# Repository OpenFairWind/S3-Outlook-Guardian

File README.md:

# Signal K Outlook Guardian

The Outlook Guardian is a talking alarm annunciator for boats: an ESP32-S3 device that listens for vessel alarms and reads them out loud.

* Speaks the message of every [Signal K](https://signalk.org) notification that is raised
* Falls back to the NMEA 2000 alert messages (PGN 126983 and 126985) when the Signal K server is not connected
* Shows the severity of the alarm on the on-board RGB LED, which flashes red if the audio output fails to start
* Shows the IP address, the WiFi mode, the stream status and the latest notification on an optional SSD1306 OLED display
* Two push buttons acknowledge and snooze the alarms, and tell the Signal K server so
* The Signal K notification paths and the NMEA 2000 alert types to announce, and the welcome message, are chosen in the web interface
* Six languages (US and UK English, Italian, German, Spanish, French) with a choice of voice, speed and volume in the web interface
* Speech is synthesized on the device with PicoTTS and played through a MAX98357A I2S amplifier; no internet connection is needed

It is built with SensESP, and this repository is a fork of [SignalK/SensESP](https://github.com/SignalK/SensESP) that adds the application and the drivers it needs.

## Hardware

* ESP32-S3-DevKitC-1 N16R8 (16 MB flash, 8 MB PSRAM)
* MAX98357A I2S amplifier and a speaker
* 3.3 V CAN transceiver for the NMEA 2000 bus
* Two push buttons
* SSD1306 128x64 I2C OLED display (optional)

| Function | GPIO |
|----------|------|
| Amplifier LRC / BCLK / DIN | 4 / 5 / 6 |
| CAN TX / RX | 17 / 18 |
| Acknowledge button | 15 |
| Snooze button | 16 |
| Display SDA / SCL | 8 / 9 |
| RGB LED | 48 |

## Building and flashing

```sh
git clone --recursive https://github.com/OpenFairWind/S3-Outlook-Guardian.git
cd S3-Outlook-Guardian
pio run -e pioarduino_esp32s3 -t upload
```

The firmware is updated over USB. Over-the-air updates are not available, because the firmware with all six languages is too large to fit twice in the flash.

## Using it

On the first start the device opens a WiFi access point called `outlook-guardian`, with the password `thisisfine`, for entering the boat's WiFi settings at `http://192.168.4.1/`.
Approve its access request on the Signal K server with read/write permission, then open `http://outlook-guardian.local/` and choose the language and voice under *Speech and alarms*.

| LED | Meaning |
|-----|---------|
| Off | No alarm |
| Blue | Alert or caution |
| Yellow | Warning |
| Red | Alarm |
| Red, blinking fast | Emergency |

The LED blinks until the alarms have been acknowledged or snoozed.

## Outlook Guardian documentation

A step-by-step guide, from a bare board to a speaking device, is in [`docs/pages/outlook_guardian`](docs/pages/outlook_guardian/index.md):

1. [Assemble the hardware](docs/pages/outlook_guardian/hardware.md)
2. [Install the software and flash the firmware](docs/pages/outlook_guardian/building.md)
3. [Connect to WiFi and Signal K](docs/pages/outlook_guardian/first_start.md)
4. [Configure and test](docs/pages/outlook_guardian/usage.md)

Reference:

* [Alarm sources](docs/pages/outlook_guardian/alarm_sources.md) - how Signal K notifications and NMEA 2000 alerts are handled
* [Development notes](docs/pages/outlook_guardian/development.md) - code structure, languages and flash layout

## Status

The firmware builds, flashes and starts on the board. The audio output, the handling of live Signal K notifications and the reception of NMEA 2000 alerts have not yet been tested against real equipment.

## License

* Firmware and everything else in this repository: Apache License 2.0, see [LICENSE](LICENSE)
* Outlook Guardian board design in [hardware/outlook_guardian](hardware/outlook_guardian): [CC BY 4.0](https://creativecommons.org/licenses/by/4.0/), see [hardware/outlook_guardian/LICENSE](hardware/outlook_guardian/LICENSE)

# About SensESP

The rest of this file is the README of SensESP, the framework this project is built on.

## Introduction

**TL;DR: [Click here for the Getting Started documentation!](https://signalk.org/SensESP/pages/getting_started/)**

SensESP is a [Signal K](https://signalk.org) sensor development toolkit for the [ESP32](https://en.wikipedia.org/wiki/ESP32) platform.
If you are a boater (or a professional developer!) who wants to build a custom Wi-Fi connected sensor for your boat, this is the toolkit you need.
SensESP runs on commonly available ESP32 boards and helps you get sensor readings from physical sensors and transform them to meaningful data for Signal K or other outputs.

SensESP is built on the [Arduino](https://github.com/espressif/arduino-esp32) software development framework, a popular open source platform for embedded development.
(Note that this refers only to the software stack - Arduino hardware is not supported.)
To automate the management of external libraries, it also heavily relies on PlatformIO, a cross-platform build system for embedded devices (in other words, Arduino IDE is not supported).

SensESP features include:

* High-level programming interfaces for sensor development
* Support for a wide range of common sensor hardware with a set of [add-on libraries](https://signalk.org/SensESP/pages/additional_resources/) - and if native support is missing, using existing Arduino libraries directly is also quite simple in most cases
* A Web configuration user interface for sensors, transforms, and output paths
* Easy on-boarding with a Wi-Fi configuration tool and fully automated server discovery
* Full Signal K integration with authentication, and transmission and reception of data
* Support for over-the-air (OTA) firmware updates
* Support for remote debugging over Wi-Fi

To use SensESP, you need an ESP32 development board and a way to power it from the boat's 12V or 24V nominal power system.
This can be done with commonly available ESP32DevKit boards and external DC-DC converters, or alternatively, the [Sailor Hat with ESP32 (SH-ESP32)](https://hatlabs.fi/product/sailor-hat-with-esp32/) has all these features baked into a developer-friendly board and enclosure kit.

Example use cases of SensESP include:

* Engine temperature measurement
* Switch input for bilge alarms
* Device control using relays
* Custom GPS and attitude sensors
* Engine RPM measurement
* Anchor chain counter
* Battery voltage and current measurement
* Tank level measurement
* Custom NMEA 2000 sensors

At heart, SensESP is a development toolkit, and not ready-made software.
This means that you will need to do some simple programming to use it.
Don't worry, though.
The project is newbie-friendly, so you don't need to know much to get started.
A lot of examples and tutorials are provided, and some related projects also provide ready-to-use firmware for specific use cases.

> **Prefer an AI-assisted path?** The [SensESP Workspace](https://github.com/hatlabs/SensESP-workspace)
> is a [Claude Code](https://code.claude.com/docs/en/quickstart) environment that
> guides you from a natural-language description of what you want to build all the
> way to firmware flashed on your device — no prior embedded experience required.
> It supports Hat Labs boards (HALMET, HALSER, SH-ESP32, SH-wg) and generic ESP32s.

## Documentation

To get started, [see the project documentation](https://signalk.org/SensESP/).

For reference, the old SensESP version 1 documentation is still available at the [repository wiki](https://github.com/SignalK/SensESP/wiki).

## Getting help

Discussion about SensESP happens mostly on the [Signal K Discord](https://discord.com/channels/1170433917761892493/1170433918592368684) on the #sensesp channel. To register as a new user, follow the invite link at [signalk.org](https://signalk.org/).

Another place for SensESP discussions is the [discussion board on the SensESP GitHub repository](https://github.com/SignalK/SensESP/discussions).

## Version 3

SensESP v3 is the current major version. Key changes from v2 include:

- Web frontend rewritten with Preact and Bootstrap, replacing the old JSONEditor-based UI
- Built-in WiFi manager replacing the external WiFiManager library, with simultaneous AP+STA support
- Explicit `ConfigItem` system for exposing objects to the web configuration UI
- Transport-agnostic networking supporting both WiFi and Ethernet
- New transforms: Join, Zip, Filter, Throttle, Repeat variants, Hysteresis
- Standard ESP-IDF logging replacing RemoteDebug

For migration instructions from v2, see the [Migration Guide](https://signalk.org/SensESP/pages/migration/).

### Development

The frontend project is in the `frontend` directory tree. To build the frontend,
you need to have Node and `pnpm` installed. Install the required dependencies:

```sh
./run install-frontend
```

Then build the frontend:

```sh
./run build-frontend
```

This will both build the project and save the deployment files in C++ source files suitable for embedding in the SensESP firmware.

To start the development server, run:

```sh
cd frontend
pnpm run dev
```

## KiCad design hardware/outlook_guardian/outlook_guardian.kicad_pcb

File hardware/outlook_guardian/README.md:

# Outlook Guardian board

A KiCad 10 project for a single board that replaces the breadboard build described in
[the hardware guide](../../docs/pages/outlook_guardian/hardware.md).

**Status: revision 0.1, not yet built.** The schematic passes ERC and the board passes DRC, but no
board has been made and no engineer has reviewed the layout. Read [Before ordering](#before-ordering)
first.

## Form factor

The board follows the [Hat Labs HALMET](https://github.com/hatlabs/HALMET-hardware) (CC BY 4.0), so it
fits the same 100 x 68 x 50 mm enclosure. These are at HALMET's exact positions:

- the outline (89 x 58 mm, concave corners, tab on the right) and the two M3 slots,
- the module, with its antenna overhanging the board edge,
- the 2x10 GPIO header and the 1x4 display socket, with the same power and ground pins,
- the NMEA 2000 terminal block (GND, V+, CAN-H, CAN-L), the USB socket, the BOOT and RESET buttons
  and the EN/IO0 header.

HALMET uses an ESP32; this board uses the ESP32-S3-WROOM-1-N16R8 the firmware needs. The module
outline is the same, but the GPIO numbers are not, so the signal pins of the headers carry ESP32-S3
pins.

## Pins

The on-board functions use the pins the firmware already defaults to, so no build flag changes.

| Function | GPIO |
|----------|------|
| Amplifier LRC, BCLK, DIN | 4, 5, 6 |
| Display SDA, SCL | 8, 9 |
| Acknowledge, Snooze buttons | 15, 16 |
| CAN TX, RX | 17, 18 |
| USB D-, D+ | 19, 20 |
| RGB LED (SK6812) | 48 |
| BOOT button | 0 |

GPIO header (J3), pin 1 is the square pad:

| Pin | Signal | Pin | Signal |
|-----|--------|-----|--------|
| 1 | 3V3 | 2 | IO21 |
| 3 | GND | 4 | IO1 |
| 5 | IO11 | 6 | IO2 |
| 7 | IO12 | 8 | IO7 |
| 9 | IO13 | 10 | IO10 |
| 11 | IO14 | 12 | GND |
| 13 | IO41 (MTDI) | 14 | GND |
| 15 | IO40 (MTDO) | 16 | GND |
| 17 | IO39 (MTCK) | 18 | GND |
| 19 | IO42 (MTMS) | 20 | 3V3 |

Display socket (J5): GND, 3V3, SCL, SDA, with GND next to the BOOT button. UART0 TX and RX, 5 V,
3.3 V and GND are on test pads on the back.

## Circuit

- **Supply, 9 to 32 V:** resettable fuse, TVS diode, reverse-polarity Schottky, input filter, then an
  XL1509-5.0 buck converter to 5 V (the converter HALMET uses, in its 5 V version).
- **3.3 V:** linear regulator from 5 V.
- **USB:** Micro-B on the ESP32-S3's native USB, with ESD protection. USB also powers the board
  through a fuse and a diode, so USB and the boat supply can be connected together.
- **Audio:** MAX98357A at 5 V, ferrite beads and capacitors on the speaker outputs.
- **NMEA 2000:** SN65HVD230 with a TVS diode, no termination resistor.
- **Buttons:** pull-up, series resistor, capacitor and ESD diode on each input.

## Files

| File | Content |
|------|---------|
| `outlook_guardian.kicad_pro`, `.kicad_sch`, `.kicad_pcb` | The project: open the `.kicad_pro` in KiCad |
| `OutlookGuardian.pretty/` | The mounting slot and the module footprint with a narrower antenna keep-out |
| `fab/` | Gerbers and drill files (also zipped), BOM, placement file, schematic and assembly PDFs, renders |
| `tools/` | The scripts that generated the project |

The board has four layers: signals and ground pour on the outer layers, a ground plane on inner
layer 1, and 3.3 V with a 5 V area on inner layer 2.

## Regenerating

The schematic and the board were generated by the scripts in `tools/` and can be edited in KiCad like
any other project. **Running the scripts again overwrites edits made in KiCad.**

```bash
tools/check.sh    # schematic from tools/design.py, then ERC
tools/route.sh    # board from the schematic and tools/placement.py, autoroute, DRC
tools/fab.sh      # fabrication files into fab/
```

`route.sh` needs Java and the [Freerouting](https://github.com/freerouting/freerouting) 1.9.0 jar; set
`FREEROUTING` to its path. Later Freerouting versions did not terminate on this board.

## Before ordering

Checked by tools:

- ERC: one warning, the pin type of the amplifier's thermal pad in KiCad's own symbol.
- The netlist exported from the schematic matches `tools/design.py` on every pin.
- DRC: no violations, no unconnected items, no schematic mismatch, at 0.2 mm track and clearance,
  0.6/0.3 mm vias.

Not checked, and needing a person:

1. **Layout review.** The tracks come from an autorouter. Look at the buck converter loop (U1, D3,
   L2, C2 to C4), the speaker outputs and the USB pair, which is not routed as a differential pair.
2. **Antenna.** The USB socket is within the 15 mm clearance Espressif recommends around the antenna,
   as on HALMET. The module footprint's keep-out was narrowed to allow it.
3. **Part numbers.** They are in the `MPN` field. Ratings were checked against distributor listings
   for F1 and L2 only. None has a supplier order code, and none was checked for stock.
4. **F1 and D1 at 24 V.** F1 is rated 33 V and D1 is an SMBJ33CA, close to the 32 V top of the range.
   For a 24 V boat, choose a 60 V fuse and check the clamp voltage against U1's 40 V maximum.
5. **U2 output capacitor.** Confirm in the AZ1117C datasheet that it is stable with ceramic
   capacitors, or change C10.
6. **USB back-feed.** With USB only, 5 V reaches the output of U1 through L2. Confirm that the
   XL1509 tolerates this, or add a diode.
7. **Display clearance.** Check the height of the parts under the display module once its
   orientation on the socket is known.
8. **A first board is a prototype.** Bring it up on a bench supply with a current limit before
   connecting it to a boat.

## Licence

The Outlook Guardian board design in this directory (schematic, PCB layout, footprints and
fabrication outputs) is licensed under
[CC BY 4.0](https://creativecommons.org/licenses/by/4.0/); the full text is in [LICENSE](LICENSE).

The outline and the connector positions derive from the Hat Labs HALMET hardware design, also
licensed under CC BY 4.0.

This covers the hardware only. The firmware in the rest of the repository stays under the
Apache License 2.0, as in the [LICENSE](../../LICENSE) file at the repository root.

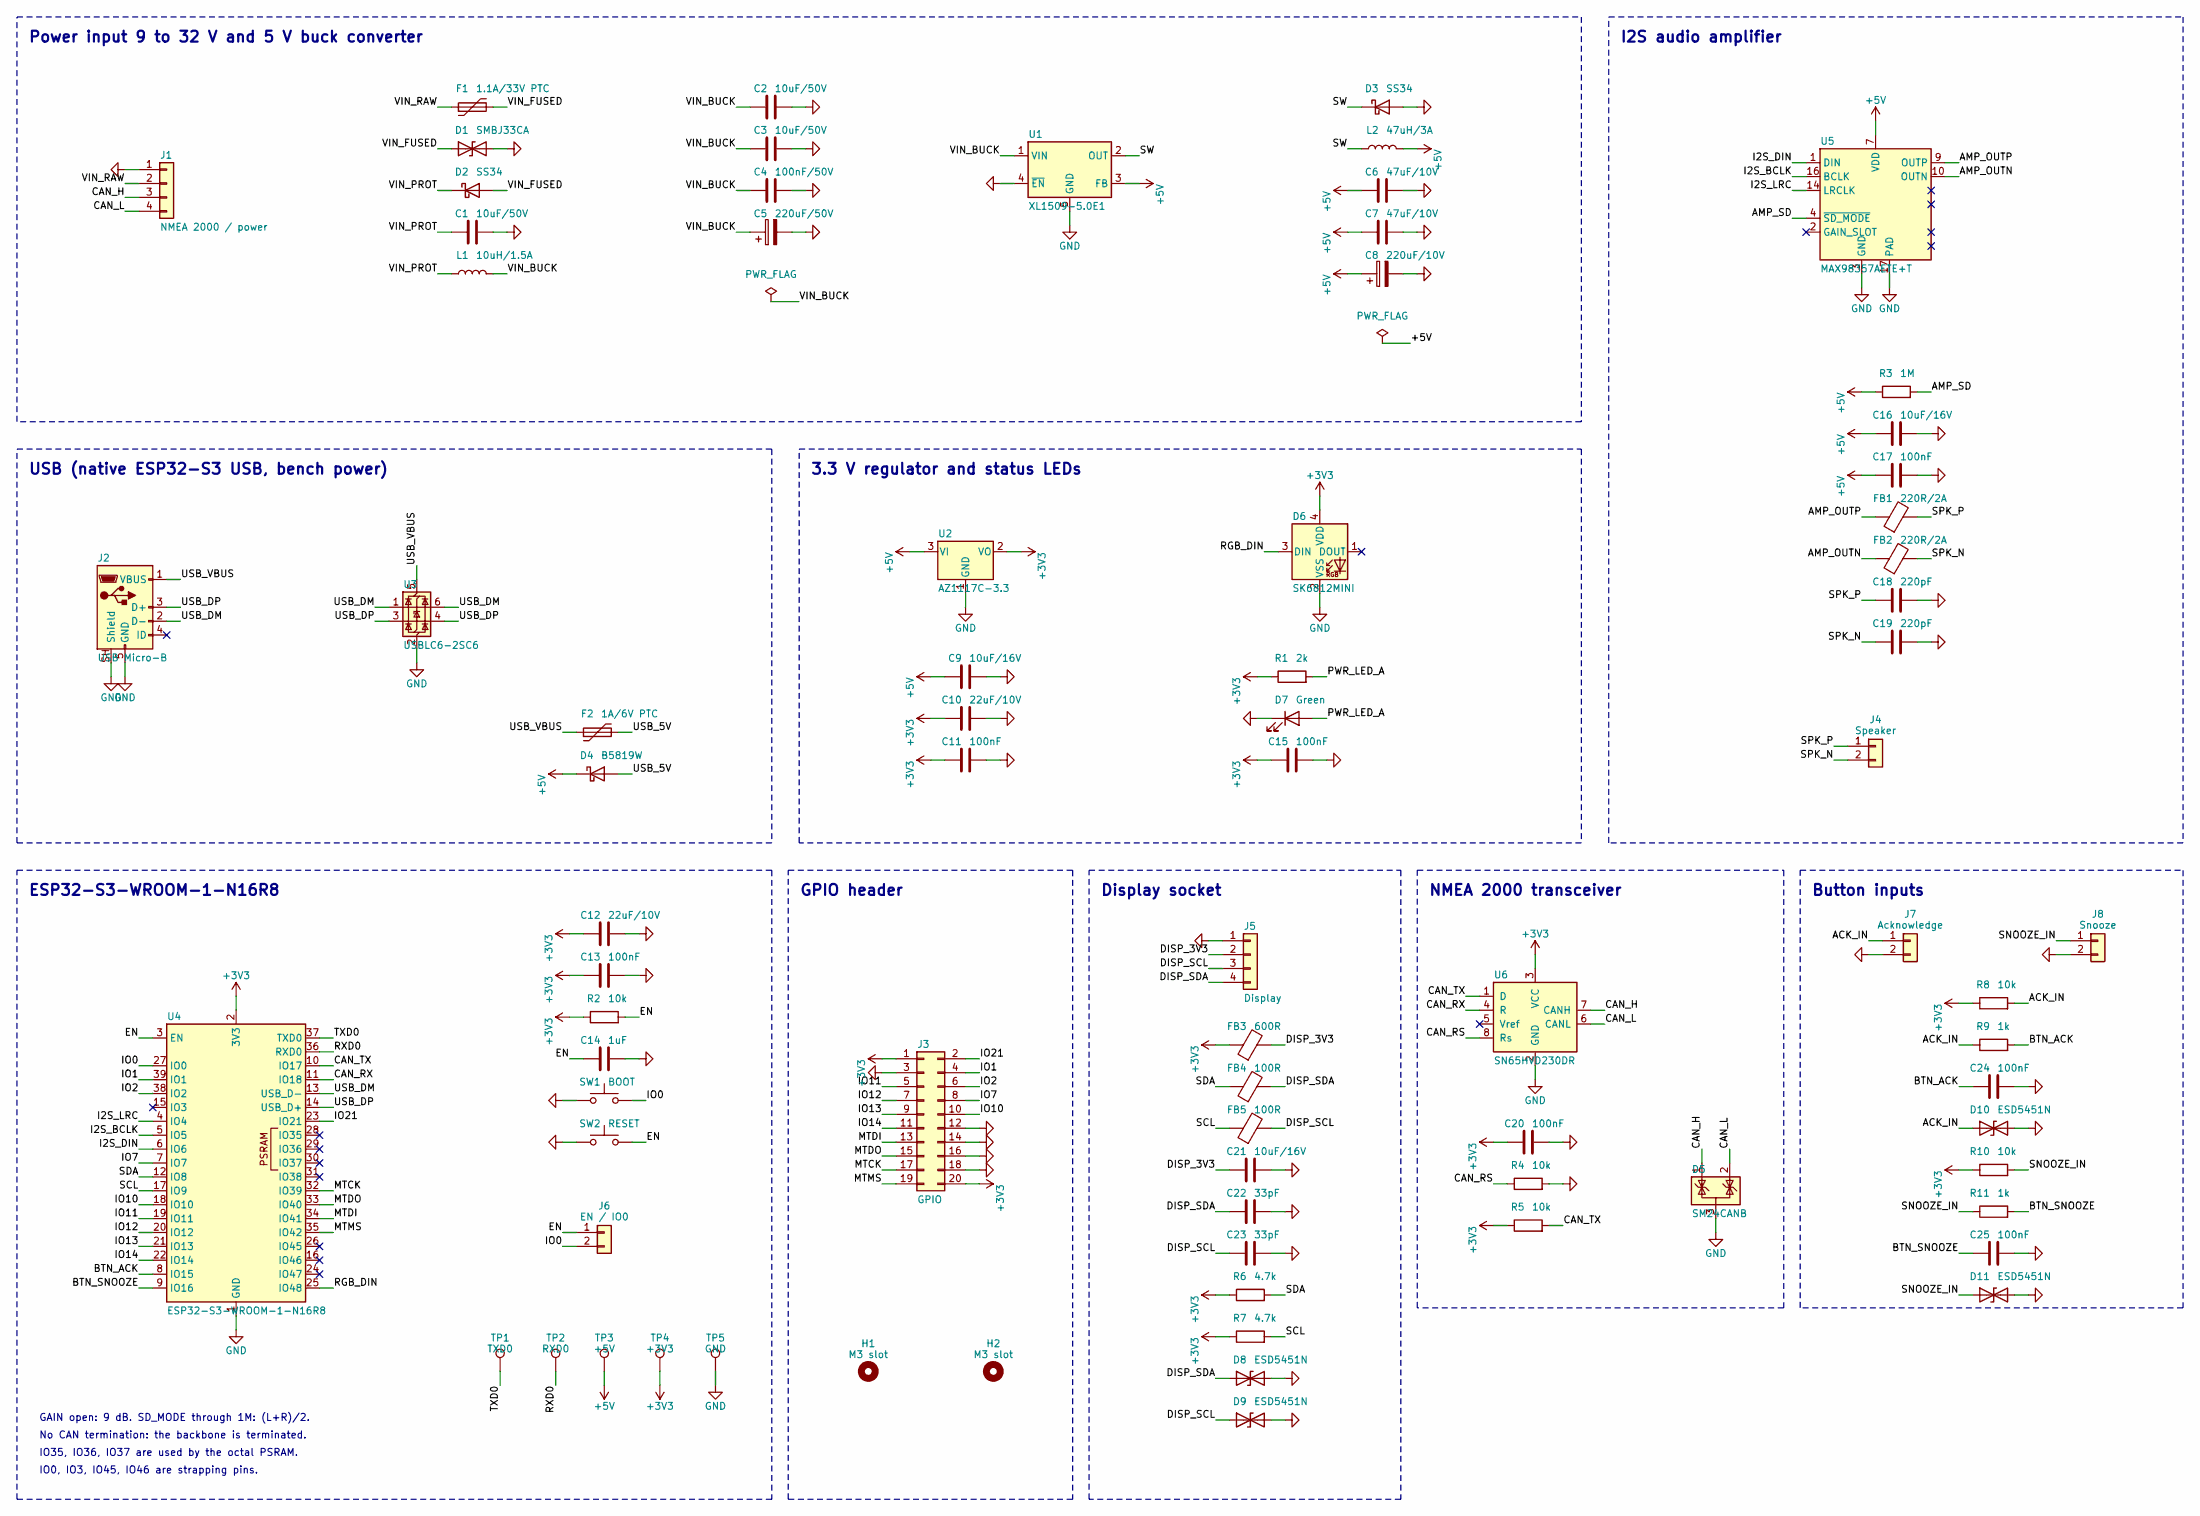
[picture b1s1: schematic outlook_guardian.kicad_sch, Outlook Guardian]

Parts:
C1, C2, C3: 10uF/50V; C_1206_3216Metric
C4: 100nF/50V; C_0603_1608Metric
C5: 220uF/50V; CP_Elec_10x10.5
C6, C7: 47uF/10V; C_1206_3216Metric
C8: 220uF/10V; CP_Elec_6.3x7.7
C9, C16, C21: 10uF/16V; C_0805_2012Metric
C10, C12: 22uF/10V; C_0805_2012Metric
C11, C13, C15, C17, C20, C24, C25: 100nF; C_0603_1608Metric
C14: 1uF; C_0603_1608Metric
C18, C19: 220pF; C_0603_1608Metric
C22, C23: 33pF; C_0603_1608Metric
D1: SMBJ33CA; D_SMB; MPN SMBJ33CA
D2, D3: SS34; D_SMA; MPN SS34
D4: B5819W; D_SOD-123; MPN B5819W
D5: SM24CANB; SOT-23; MPN SM24CANB-02HTG
D6: SK6812MINI; LED_SK6812MINI_PLCC4_3.5x3.5mm_P1.75mm; MPN SK6812MINI
D7: Green; LED_0603_1608Metric
D8, D9, D10, D11: ESD5451N; D_0402_1005Metric; MPN ESD5451N
F1: 1.1A/33V PTC; Fuse_1812_4532Metric; MPN 1812L110/33MR
F2: 1A/6V PTC; Fuse_1206_3216Metric; MPN BSMD1206-100-6V
FB1, FB2: 220R/2A; L_0805_2012Metric; MPN BLM21PG221SN1D
FB3: 600R; L_0805_2012Metric; MPN GZ2012D601TF
FB4, FB5: 100R; L_0805_2012Metric; MPN GZ2012D101TF
H1, H2: M3 slot; MountingSlot_3.2mm_M3_Unplated
J1: NMEA 2000 / power; PhoenixContact_MCV_1,5_4-G-3.81_1x04_P3.81mm_Vertical; MPN Phoenix MCV 1,5/4-G-3,81
J2: USB Micro-B; USB_Micro-B_Wuerth_614105150721_Vertical; MPN Wuerth 614105150721
J3: GPIO; PinHeader_2x10_P2.54mm_Vertical
J4: Speaker; PhoenixContact_MCV_1,5_2-G-3.81_1x02_P3.81mm_Vertical; MPN Phoenix MCV 1,5/2-G-3,81
J5: Display; PinSocket_1x04_P2.54mm_Vertical
J6: EN / IO0; PinHeader_1x02_P2.54mm_Vertical
J7: Acknowledge; PhoenixContact_MCV_1,5_2-G-3.81_1x02_P3.81mm_Vertical; MPN Phoenix MCV 1,5/2-G-3,81
J8: Snooze; PhoenixContact_MCV_1,5_2-G-3.81_1x02_P3.81mm_Vertical; MPN Phoenix MCV 1,5/2-G-3,81
L1: 10uH/1.5A; L_Bourns-SRN4018; MPN SRN4018-100M
L2: 47uH/3A; L_Bourns_SRR1260; MPN SRR1260-470M
R1: 2k; R_0603_1608Metric
R2, R4, R5, R8, R10: 10k; R_0603_1608Metric
R3: 1M; R_0603_1608Metric
R6, R7: 4.7k; R_0603_1608Metric
R9, R11: 1k; R_0603_1608Metric
SW1: BOOT; SW_SPST_TL3342; MPN TL3342F160QG
SW2: RESET; SW_SPST_TL3342; MPN TL3342F160QG
TP1: TXD0; TestPoint_Pad_D1.5mm
TP2: RXD0; TestPoint_Pad_D1.5mm
TP3: +5V; TestPoint_Pad_D1.5mm
TP4: +3V3; TestPoint_Pad_D1.5mm
TP5: GND; TestPoint_Pad_D1.5mm
U1: XL1509-5.0E1; SOIC-8_3.9x4.9mm_P1.27mm; MPN XL1509-5.0E1
U2: AZ1117C-3.3; SOT-223-3_TabPin2; MPN AZ1117CH-3.3TRG1
U3: USBLC6-2SC6; SOT-23-6; MPN USBLC6-2SC6
U4: ESP32-S3-WROOM-1-N16R8; ESP32-S3-WROOM-1_EdgeAntenna; MPN ESP32-S3-WROOM-1-N16R8
U5: MAX98357AETE+T; TQFN-16-1EP_3x3mm_P0.5mm_EP1.23x1.23mm; MPN MAX98357AETE+T
U6: SN65HVD230DR; SOIC-8_3.9x4.9mm_P1.27mm; MPN SN65HVD230DR

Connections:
+3V3: C10.1, C11.1, C12.1, C13.1, C15.1, C20.1, D6.4 (VDD), FB3.1, J3.1, J3.20, R1.1, R2.1, R5.1, R6.1, R7.1, R8.1, R10.1, TP4.1, U2.2 (VO), U4.2 (3V3), U6.3 (VCC)
+5V: C6.1, C7.1, C8.1, C9.1, C16.1, C17.1, D4.1 (K), L2.2, R3.1, TP3.1, U1.3 (FB), U2.3 (VI), U5.7 (VDD), U5.8 (VDD)
/ACK_IN: D10.1 (A1), J7.1, R8.2, R9.1
/AMP_OUTN: FB2.1, U5.10 (OUTN)
/AMP_OUTP: FB1.1, U5.9 (OUTP)
/AMP_SD: R3.2, U5.4 (~SD_MODE)
/BTN_ACK: C24.1, R9.2, U4.8 (IO15)
/BTN_SNOOZE: C25.1, R11.2, U4.9 (IO16)
/CAN_H: D5.1 (K), J1.3, U6.7 (CANH)
/CAN_L: D5.2 (K), J1.4, U6.6 (CANL)
/CAN_RS: R4.1, U6.8 (Rs)
/CAN_RX: U4.11 (IO18), U6.4 (R)
/CAN_TX: R5.2, U4.10 (IO17), U6.1 (D)
/DISP_3V3: C21.1, FB3.2, J5.2
/DISP_SCL: C23.1, D9.1 (A1), FB5.2, J5.3
/DISP_SDA: C22.1, D8.1 (A1), FB4.2, J5.4
/EN: C14.1, J6.1, R2.2, SW2.2, U4.3 (EN)
/I2S_BCLK: U4.5 (IO5), U5.16 (BCLK)
/I2S_DIN: U4.6 (IO6), U5.1 (DIN)
/I2S_LRC: U4.4 (IO4), U5.14 (LRCLK)
/IO0: J6.2, SW1.2, U4.27 (IO0)
/IO1: J3.4, U4.39 (IO1)
/IO2: J3.6, U4.38 (IO2)
/IO7: J3.8, U4.7 (IO7)
/IO10: J3.10, U4.18 (IO10)
/IO11: J3.5, U4.19 (IO11)
/IO12: J3.7, U4.20 (IO12)
/IO13: J3.9, U4.21 (IO13)
/IO14: J3.11, U4.22 (IO14)
/IO21: J3.2, U4.23 (IO21)
/MTCK: J3.17, U4.32 (IO39)
/MTDI: J3.13, U4.34 (IO41)
/MTDO: J3.15, U4.33 (IO40)
/MTMS: J3.19, U4.35 (IO42)
/PWR_LED_A: D7.2 (A), R1.2
/RGB_DIN: D6.3 (DIN), U4.25 (IO48)
/RXD0: TP2.1, U4.36 (RXD0)
/SCL: FB5.1, R7.2, U4.17 (IO9)
/SDA: FB4.1, R6.2, U4.12 (IO8)
/SNOOZE_IN: D11.1 (A1), J8.1, R10.2, R11.1
/SPK_N: C19.1, FB2.2, J4.2
/SPK_P: C18.1, FB1.2, J4.1
/SW: D3.1 (K), L2.1, U1.2 (OUT)
/TXD0: TP1.1, U4.37 (TXD0)
/USB_5V: D4.2 (A), F2.2
/USB_DM: J2.2 (D-), U3.1 (I/O1), U3.6 (I/O1), U4.13 (USB_D-)
/USB_DP: J2.3 (D+), U3.3 (I/O2), U3.4 (I/O2), U4.14 (USB_D+)
/USB_VBUS: F2.1, J2.1 (VBUS), U3.5 (VBUS)
/VIN_BUCK: C2.1, C3.1, C4.1, C5.1, L1.2, U1.1 (VIN)
/VIN_FUSED: D1.1 (A1), D2.2 (A), F1.2
/VIN_PROT: C1.1, D2.1 (K), L1.1
/VIN_RAW: F1.1, J1.2
GND: C1.2, C2.2, C3.2, C4.2, C5.2, C6.2, C7.2, C8.2, C9.2, C10.2, C11.2, C12.2, C13.2, C14.2, C15.2, C16.2, C17.2, C18.2, C19.2, C20.2, C21.2, C22.2, C23.2, C24.2, C25.2, D1.2 (A2), D3.2 (A), D5.3 (A), D6.2 (VSS), D7.1 (K), D8.2 (A2), D9.2 (A2), D10.2 (A2), D11.2 (A2), J1.1, J2.5 (GND), J2.SH (Shield), J3.3, J3.12, J3.14, J3.16, J3.18, J5.1, J7.2, J8.2, R4.2, SW1.1, SW2.1, TP5.1, U1.4 (~EN), U1.5 (GND), U1.6 (GND), U1.7 (GND), U1.8 (GND), U2.1 (GND), U3.2 (GND), U4.1 (GND), U4.40 (GND), U4.41 (GND), U5.3 (GND), U5.11 (GND), U5.15 (GND), U5.17 (PAD), U6.2 (GND)

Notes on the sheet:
IO0, IO3, IO45, IO46 are strapping pins.
ESP32-S3-WROOM-1-N16R8
3.3 V regulator and status LEDs
I2S audio amplifier
NMEA 2000 transceiver
USB (native ESP32-S3 USB, bench power)
Power input 9 to 32 V and 5 V buck converter
GPIO header
No CAN termination: the backbone is terminated.
GAIN open: 9 dB. SD_MODE through 1M: (L+R)/2.
Display socket
IO35, IO36, IO37 are used by the octal PSRAM.
Button inputs

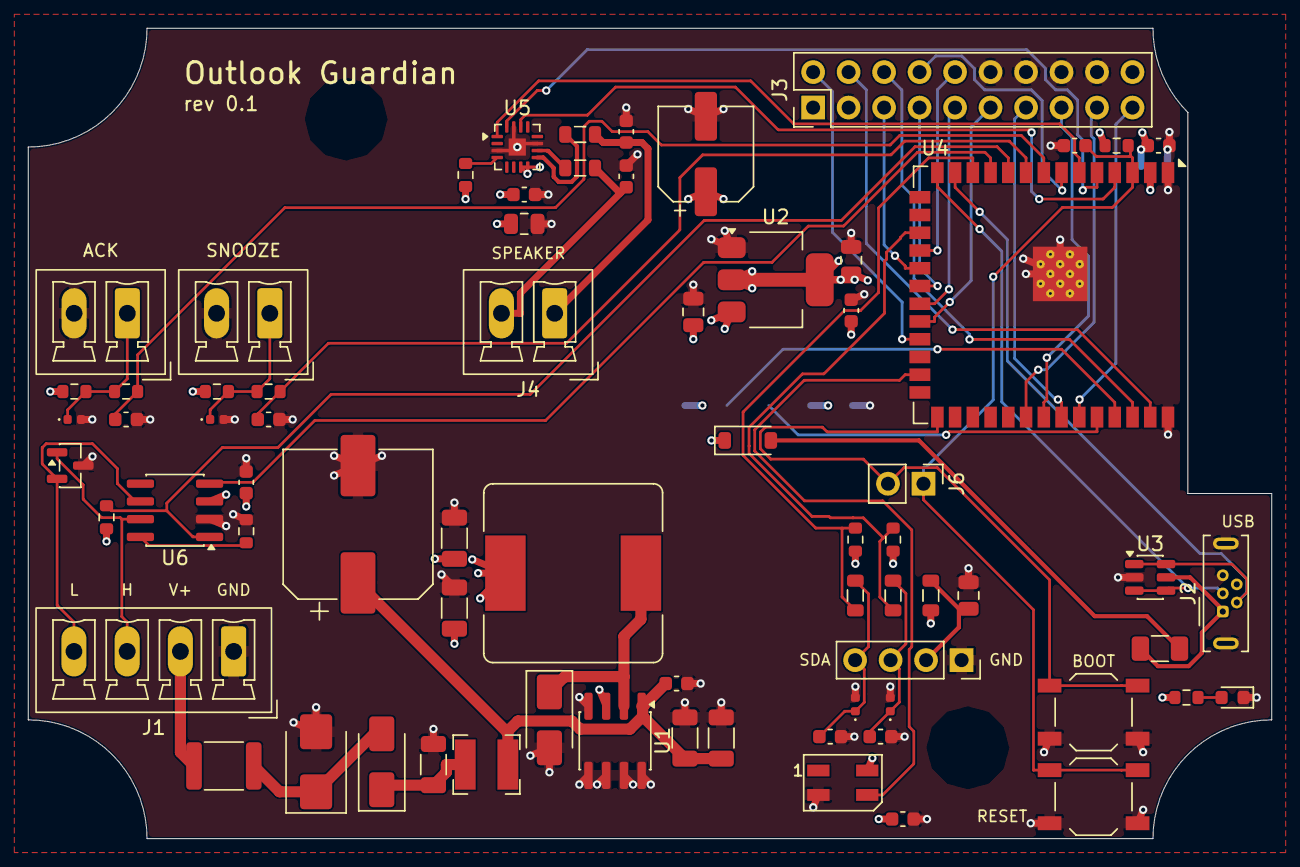
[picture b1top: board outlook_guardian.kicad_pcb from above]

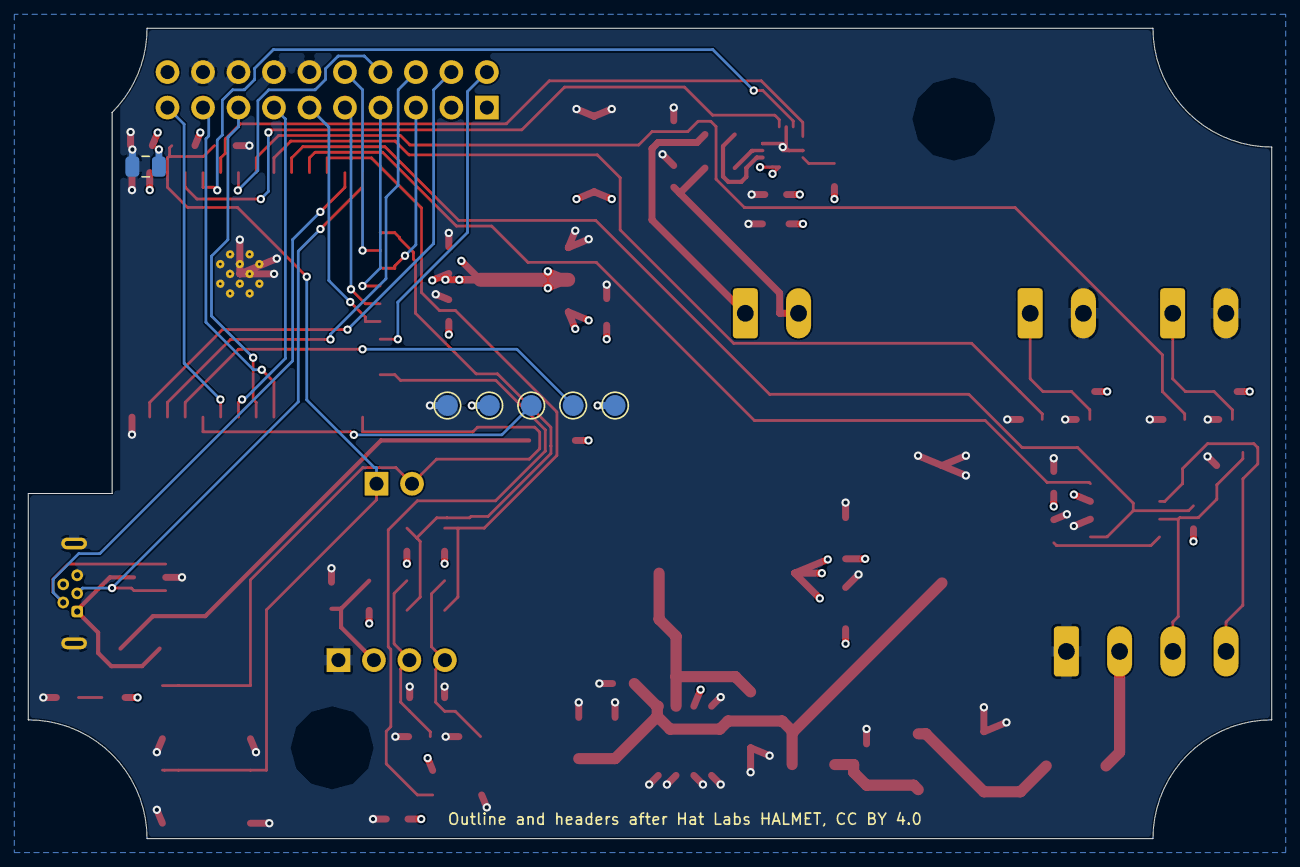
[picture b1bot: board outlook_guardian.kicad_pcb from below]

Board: 4 copper layers, 89.0 x 58.0 mm, 79 parts (6 on the bottom side), 53 nets.

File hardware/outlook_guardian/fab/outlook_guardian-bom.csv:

"Reference","Value","Footprint","MPN","Qty"
"C1,C2,C3","10uF/50V","Capacitor_SMD:C_1206_3216Metric","","3"
"C4","100nF/50V","Capacitor_SMD:C_0603_1608Metric","","1"
"C5","220uF/50V","Capacitor_SMD:CP_Elec_10x10.5","","1"
"C6,C7","47uF/10V","Capacitor_SMD:C_1206_3216Metric","","2"
"C8","220uF/10V","Capacitor_SMD:CP_Elec_6.3x7.7","","1"
"C9,C16,C21","10uF/16V","Capacitor_SMD:C_0805_2012Metric","","3"
"C10,C12","22uF/10V","Capacitor_SMD:C_0805_2012Metric","","2"
"C11,C13,C15,C17,C20,C24,C25","100nF","Capacitor_SMD:C_0603_1608Metric","","7"
"C14","1uF","Capacitor_SMD:C_0603_1608Metric","","1"
"C18,C19","220pF","Capacitor_SMD:C_0603_1608Metric","","2"
"C22,C23","33pF","Capacitor_SMD:C_0603_1608Metric","","2"
"D1","SMBJ33CA","Diode_SMD:D_SMB","SMBJ33CA","1"
"D2,D3","SS34","Diode_SMD:D_SMA","SS34","2"
"D4","B5819W","Diode_SMD:D_SOD-123","B5819W","1"
"D5","SM24CANB","Package_TO_SOT_SMD:SOT-23","SM24CANB-02HTG","1"
"D6","SK6812MINI","LED_SMD:LED_SK6812MINI_PLCC4_3.5x3.5mm_P1.75mm","SK6812MINI","1"
"D7","Green","LED_SMD:LED_0603_1608Metric","","1"
"D8,D9,D10,D11","ESD5451N","Diode_SMD:D_0402_1005Metric","ESD5451N","4"
"F1","1.1A/33V PTC","Fuse:Fuse_1812_4532Metric","1812L110/33MR","1"
"F2","1A/6V PTC","Fuse:Fuse_1206_3216Metric","BSMD1206-100-6V","1"
"FB1,FB2","220R/2A","Inductor_SMD:L_0805_2012Metric","BLM21PG221SN1D","2"
"FB3","600R","Inductor_SMD:L_0805_2012Metric","GZ2012D601TF","1"
"FB4,FB5","100R","Inductor_SMD:L_0805_2012Metric","GZ2012D101TF","2"
"J1","NMEA 2000 / power","Connector_Phoenix_MC:PhoenixContact_MCV_1,5_4-G-3.81_1x04_P3.81mm_Vertical","Phoenix MCV 1,5/4-G-3,81","1"
"J2","USB Micro-B","Connector_USB:USB_Micro-B_Wuerth_614105150721_Vertical","Wuerth 614105150721","1"
"J3","GPIO","Connector_PinHeader_2.54mm:PinHeader_2x10_P2.54mm_Vertical","","1"
"J4","Speaker","Connector_Phoenix_MC:PhoenixContact_MCV_1,5_2-G-3.81_1x02_P3.81mm_Vertical","Phoenix MCV 1,5/2-G-3,81","1"
"J5","Display","Connector_PinSocket_2.54mm:PinSocket_1x04_P2.54mm_Vertical","","1"
"J6","EN / IO0","Connector_PinHeader_2.54mm:PinHeader_1x02_P2.54mm_Vertical","","1"
"J7","Acknowledge","Connector_Phoenix_MC:PhoenixContact_MCV_1,5_2-G-3.81_1x02_P3.81mm_Vertical","Phoenix MCV 1,5/2-G-3,81","1"
"J8","Snooze","Connector_Phoenix_MC:PhoenixContact_MCV_1,5_2-G-3.81_1x02_P3.81mm_Vertical","Phoenix MCV 1,5/2-G-3,81","1"
"L1","10uH/1.5A","Inductor_SMD:L_Bourns-SRN4018","SRN4018-100M","1"
"L2","47uH/3A","Inductor_SMD:L_Bourns_SRR1260","SRR1260-470M","1"
"R1","2k","Resistor_SMD:R_0603_1608Metric","","1"
"R2,R4,R5,R8,R10","10k","Resistor_SMD:R_0603_1608Metric","","5"
"R3","1M","Resistor_SMD:R_0603_1608Metric","","1"
"R6,R7","4.7k","Resistor_SMD:R_0603_1608Metric","","2"
"R9,R11","1k","Resistor_SMD:R_0603_1608Metric","","2"
"SW1","BOOT","Button_Switch_SMD:SW_SPST_TL3342","TL3342F160QG","1"
"SW2","RESET","Button_Switch_SMD:SW_SPST_TL3342","TL3342F160QG","1"
"U1","XL1509-5.0E1","Package_SO:SOIC-8_3.9x4.9mm_P1.27mm","XL1509-5.0E1","1"
"U2","AZ1117C-3.3","Package_TO_SOT_SMD:SOT-223-3_TabPin2","AZ1117CH-3.3TRG1","1"
"U3","USBLC6-2SC6","Package_TO_SOT_SMD:SOT-23-6","USBLC6-2SC6","1"
"U4","ESP32-S3-WROOM-1-N16R8","OutlookGuardian:ESP32-S3-WROOM-1_EdgeAntenna","ESP32-S3-WROOM-1-N16R8","1"
"U5","MAX98357AETE+T","Package_DFN_QFN:TQFN-16-1EP_3x3mm_P0.5mm_EP1.23x1.23mm","MAX98357AETE+T","1"
"U6","SN65HVD230DR","Package_SO:SOIC-8_3.9x4.9mm_P1.27mm","SN65HVD230DR","1"

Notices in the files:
hardware/outlook_guardian/outlook_guardian.kicad_pcb:
Form factor, GPIO and display headers after Hat Labs HALMET (CC BY 4.0)
Outline and headers after Hat Labs HALMET, CC BY 4.0
